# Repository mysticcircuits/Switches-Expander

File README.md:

# Switches-Expander

Files for the Switches Turing Machine Expander module by Mystic Circuits.

This module comes with an open source licence, CC-BY-SA 3.0. Go ahead and read the licence page for more details. This means that there are no commercial restrictions on this module. Please be reasonable in your interpretation of this rule. I fully support people building their own circuit boards and even trading amongst their friends for them. However organizing group buys for these PCBs or selling the PCBs on your own will compete directly with my own products, since I sell PCBs on my website and also provide the build documentation and support. In short - don't be a shmuck about it or else I will stop open sourcing my designs.

Also note that this module is made to function with my "Universal Front Plate" PCB which is hosted in another branch. It can make the schematic a bit tricky to read sometimes but I did my best to annotate things. There might be some inconsistencies between the pin naming convention for this schematic and the one on the "UFP" schematic because this was among the first circuits that I build to work with the UFP and they both went through several revisions together.

For a description of the licence in simple terms please visit https://creativecommons.org/licenses/by-sa/3.0/

Also my build documentation uses a lot of high resolution pictures so the final size is about 45 MB. Check this link to see the build documentation as well as the BOM: https://drive.google.com/file/d/0B1jw1Qp2qZVJV1ByMFp5SVN3X0U/view?usp=drive_link&resourcekey=0-EDNIhMWUD5uWKayrew_lzA

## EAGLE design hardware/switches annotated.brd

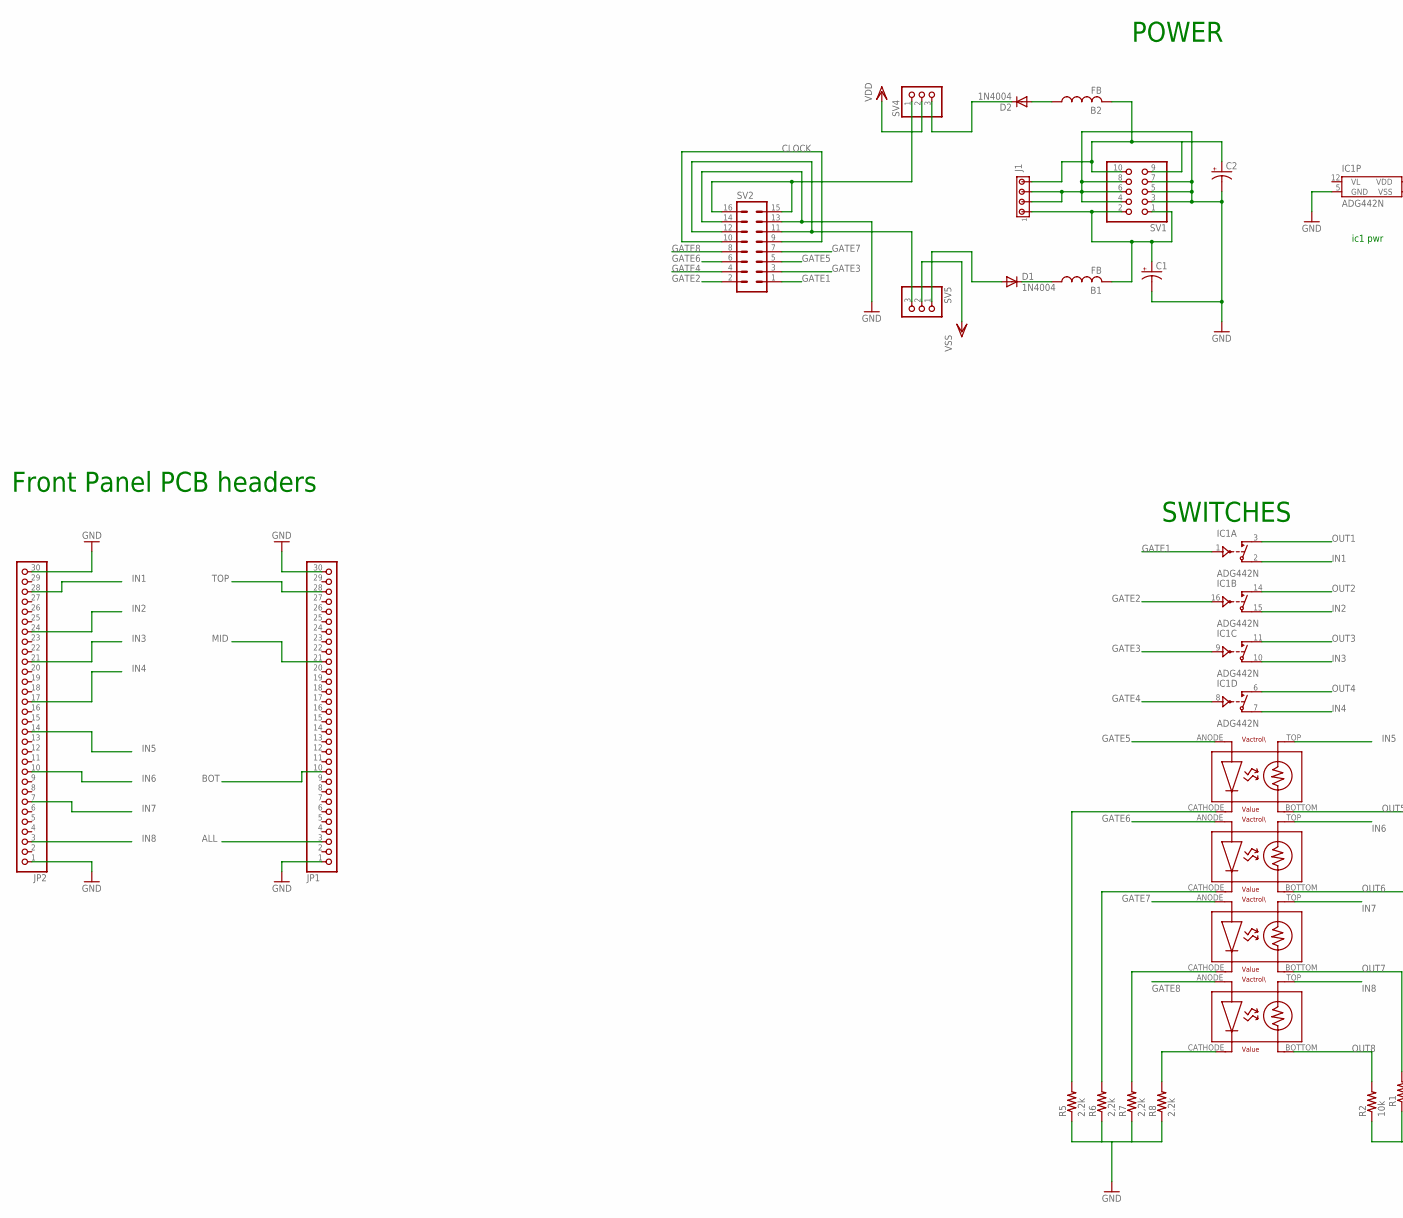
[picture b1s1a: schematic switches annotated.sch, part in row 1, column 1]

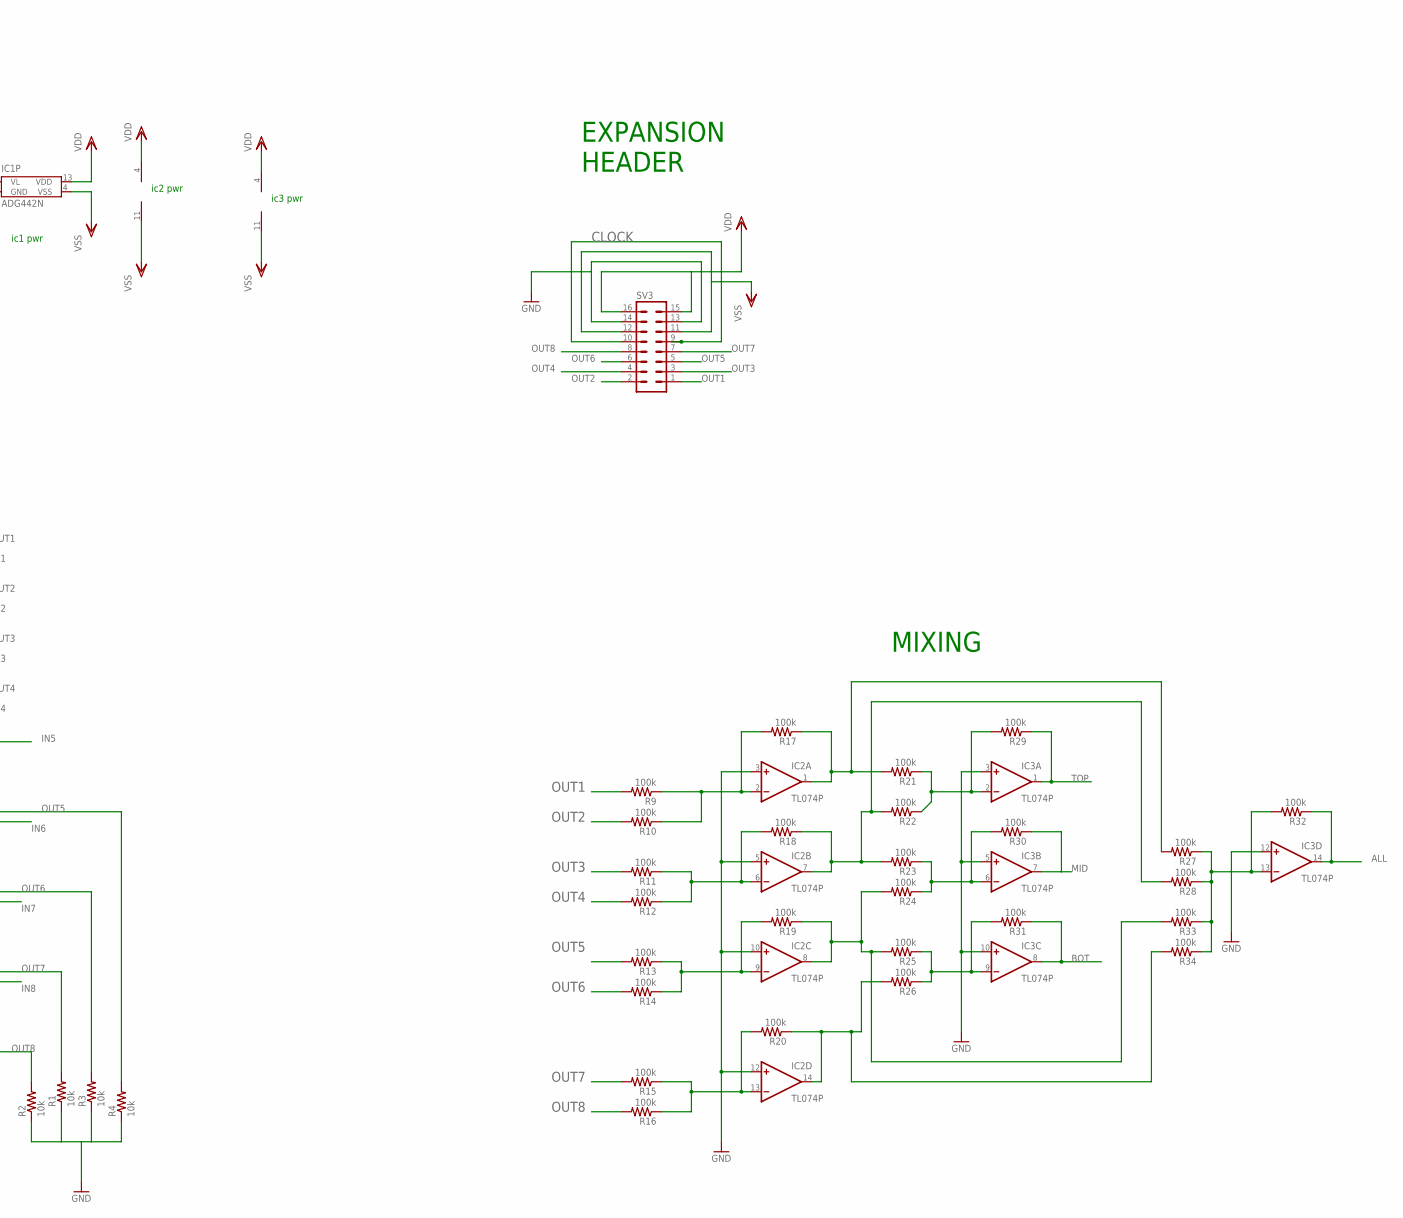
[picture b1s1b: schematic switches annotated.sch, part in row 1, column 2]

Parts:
B1, B2: FB
C1, C2: CPOL-USE1.8-4; E1,8-4
D1, D2: 1N4004; DO41-10
IC1: ADG442N; DIL16
IC2, IC3: TL074P; DIL14
J1: MTA04-156; 1X4MTA
JP1, JP2: PINHD-1X30; 1X30
R1, R2, R3, R4: 10k; 0204V
R5, R8: 2.2k; 0204V
R6, R7: 2,2k; 0204V
R9, R10, R11, R12, R13, R14, R15, R16, R21, R22, R23, R24, R26, R27, R28: 100k; 0204/7
R17, R18, R19, R20, R25, R29, R30, R31, R32, R33, R34: 100k; 0204V
SV1: PINHD-2X5; 2X05
SV2, SV3: MA08-2
SV4, SV5: PINHD-1X3; 1X03
U$1, U$2, U$3, U$4: VACTROL

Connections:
ALL: IC3.14 (OUT), JP1.3, R32.1
BOT: IC3.8 (OUT), JP1.10, R31.1
CLOCK: SV2.9, SV2.10, SV3.9, SV3.10
GATE1: IC1.1 (IN), SV2.1
GATE2: IC1.16 (IN), SV2.2
GATE3: IC1.9 (IN), SV2.3
GATE4: IC1.8 (IN), SV2.4
GATE5: SV2.5, U$1.ANODE
GATE6: SV2.6, U$2.ANODE
GATE7: SV2.7, U$3.ANODE
GATE8: SV2.8, U$4.ANODE
GND: C1.-, C2.-, IC1.5 (GND), IC2.3 (+IN), IC2.5 (+IN), IC2.10 (+IN), IC2.12 (+IN), IC3.3 (+IN), IC3.5 (+IN), IC3.10 (+IN), IC3.12 (+IN), J1.2, J1.3, JP1.1, JP1.30, JP2.1, JP2.30, R1.1, R2.1, R3.1, R4.1, R5.1, R6.1, R7.1, R8.1, SV1.3, SV1.4, SV1.5, SV1.6, SV1.7, SV1.8, SV2.13, SV2.14, SV3.13, SV3.14
IN1: IC1.2 (D), JP2.28
IN2: IC1.15 (D), JP2.24
IN3: IC1.10 (D), JP2.21
IN4: IC1.7 (D), JP2.17
IN5: JP2.14, U$1.TOP
IN6: JP2.10, U$2.TOP
IN7: JP2.7, U$3.TOP
IN8: JP2.3, U$4.TOP
MID: IC3.7 (OUT), JP1.21, R30.1
unnamed: R5.2, U$1.CATHODE
unnamed: IC2.8 (OUT), R19.1, R24.2, R25.2, R33.2
unnamed: IC2.13 (-IN), R15.1, R16.1, R20.2
unnamed: IC2.14 (OUT), R20.1, R26.2, R34.2
unnamed: IC2.9 (-IN), R13.1, R14.1, R19.2
unnamed: IC2.6 (-IN), R11.1, R12.1, R18.2
unnamed: R8.2, U$4.CATHODE
unnamed: R7.2, U$3.CATHODE
unnamed: R6.2, U$2.CATHODE
unnamed: IC2.2 (-IN), R9.1, R10.1, R17.2
unnamed: IC2.7 (OUT), R18.1, R22.2, R23.2, R28.2
unnamed: IC2.1 (OUT), R17.1, R21.2, R27.2
unnamed: IC3.9 (-IN), R25.1, R26.1, R31.2
unnamed: IC3.6 (-IN), R23.1, R24.1, R30.2
unnamed: IC3.2 (-IN), R21.1, R22.1, R29.2
unnamed: D2.C, SV4.3
unnamed: B1.P$2 (2), C1.+, J1.1, SV1.1, SV1.2
unnamed: SV2.15, SV2.16, SV4.1
unnamed: D1.A, SV5.1
unnamed: SV2.11, SV2.12, SV5.3
unnamed: B2.P$1 (1), D2.A
unnamed: B1.P$1 (1), D1.C
unnamed: B2.P$2 (2), C2.+, J1.4, SV1.9, SV1.10
unnamed: IC3.13 (-IN), R27.1, R28.1, R32.2, R33.1, R34.1
OUT1: IC1.3 (S), R9.2, SV3.1
OUT2: IC1.14 (S), R10.2, SV3.2
OUT3: IC1.11 (S), R11.2, SV3.3
OUT4: IC1.6 (S), R12.2, SV3.4
OUT5: R4.2, R13.2, SV3.5, U$1.BOTTOM
OUT6: R3.2, R14.2, SV3.6, U$2.BOTTOM
OUT7: R1.2, R15.2, SV3.7, U$3.BOTTOM
OUT8: R2.2, R16.2, SV3.8, U$4.BOTTOM
TOP: IC3.1 (OUT), JP1.28, R29.1
VDD: IC1.13 (VDD), IC2.4 (V+), IC3.4 (V+), SV3.15, SV3.16, SV4.2
VL: IC1.12 (VL)
VSS: IC1.4 (VSS), IC2.11 (V-), IC3.11 (V-), SV3.11, SV3.12, SV5.2

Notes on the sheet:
ic2 pwr
ic3 pwr
ic1 pwr
Front Panel PCB headers
POWER
EXPANSION HEADER
SWITCHES
MIXING

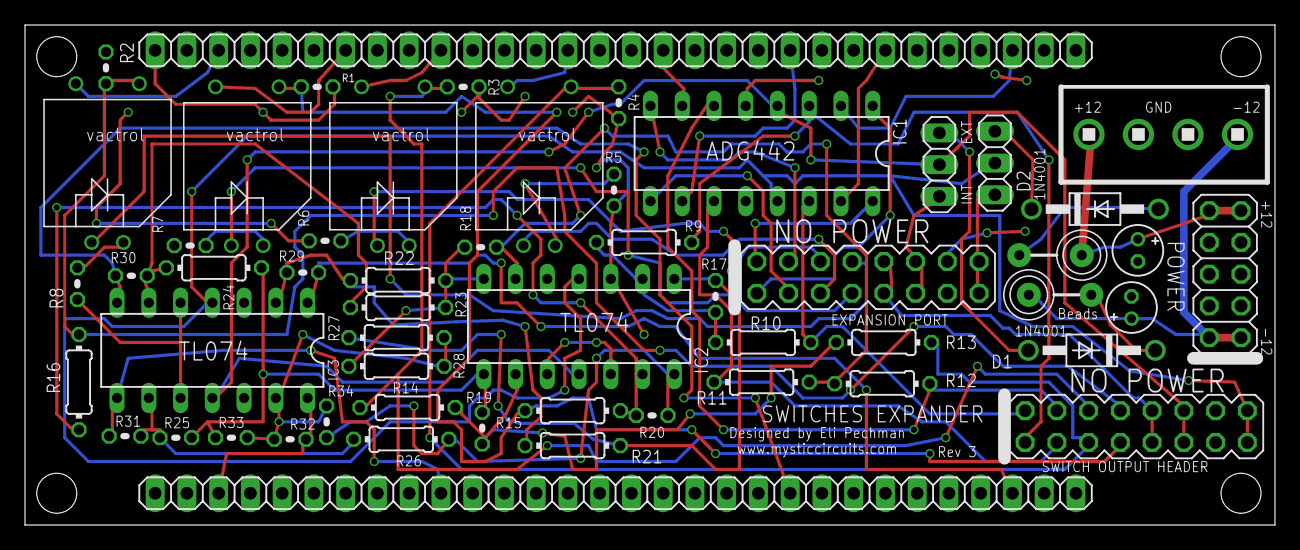
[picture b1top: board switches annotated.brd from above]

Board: 2 copper layers, 100.0 x 40.0 mm, 55 parts (0 on the bottom side), 56 nets.

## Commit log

2016-05-03 Create blah
2016-05-03 Added files via upload
2016-05-10 Create licence
2024-05-06 Update README.md
    Updated the link for the switches expander documentation
2024-05-06 Update README.md
    fixed link for switches expander documentation
